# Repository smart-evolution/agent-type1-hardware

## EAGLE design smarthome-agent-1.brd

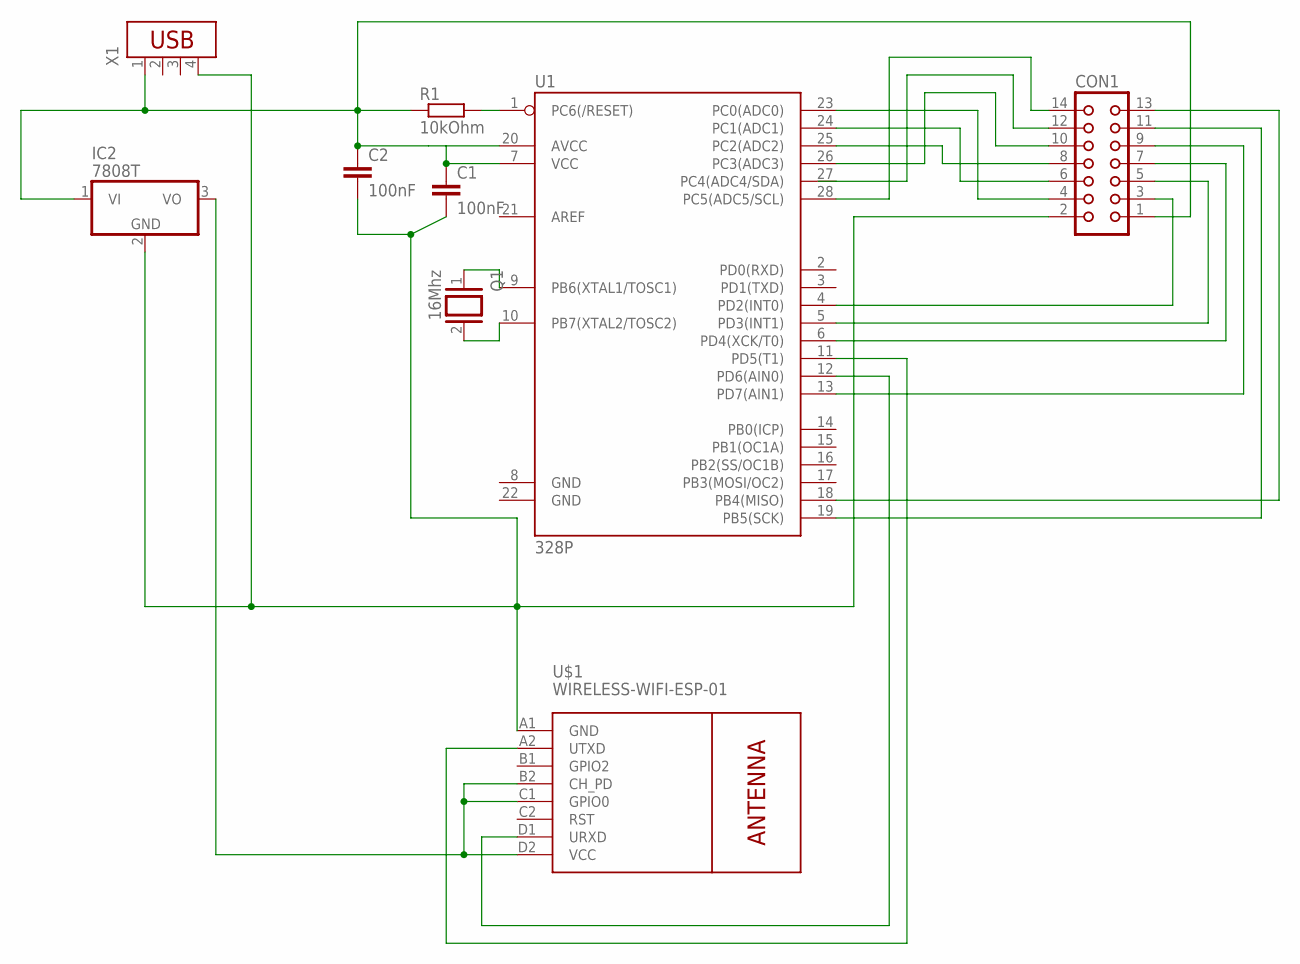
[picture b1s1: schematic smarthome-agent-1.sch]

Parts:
C1, C2: 100nF; C025-024X044
CON1: CON14
IC2: 7808T; TO220H
Q1: 16Mhz; QS
R1: 10kOhm; 0204/7
U1: 328P; DIP28
U$1: WIRELESS-WIFI-ESP-01
X1: USB-787616; USB

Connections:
unnamed: R1.2, U1.1 (PC6(/RESET))
unnamed: IC2.3 (VO), U$1.B2 (CH_PD), U$1.C1 (GPIO0), U$1.D2 (VCC)
unnamed: Q1.2, U1.10 (PB7(XTAL2/TOSC2))
unnamed: Q1.1, U1.9 (PB6(XTAL1/TOSC1))
unnamed: U1.11 (PD5(T1)), U$1.A2 (UTXD)
unnamed: U1.12 (PD6(AIN0)), U$1.D1 (URXD)
unnamed: CON1.10, U1.26 (PC3(ADC3))
unnamed: CON1.4, U1.23 (PC0(ADC0))
unnamed: CON1.6, U1.24 (PC1(ADC1))
unnamed: CON1.8, U1.25 (PC2(ADC2))
unnamed: CON1.12, U1.27 (PC4(ADC4/SDA))
unnamed: CON1.3, U1.4 (PD2(INT0))
unnamed: CON1.5, U1.5 (PD3(INT1))
unnamed: CON1.7, U1.6 (PD4(XCK/T0))
unnamed: CON1.9, U1.13 (PD7(AIN1))
unnamed: CON1.11, U1.19 (PB5(SCK))
unnamed: C1.1, C2.1, CON1.1, IC2.1 (VI), R1.1, U1.7 (VCC), U1.20 (AVCC), X1.1
unnamed: C1.2, C2.2, CON1.2, IC2.2 (GND), U$1.A1 (GND), X1.4
unnamed: CON1.13, U1.18 (PB4(MISO))
unnamed: CON1.14, U1.28 (PC5(ADC5/SCL))

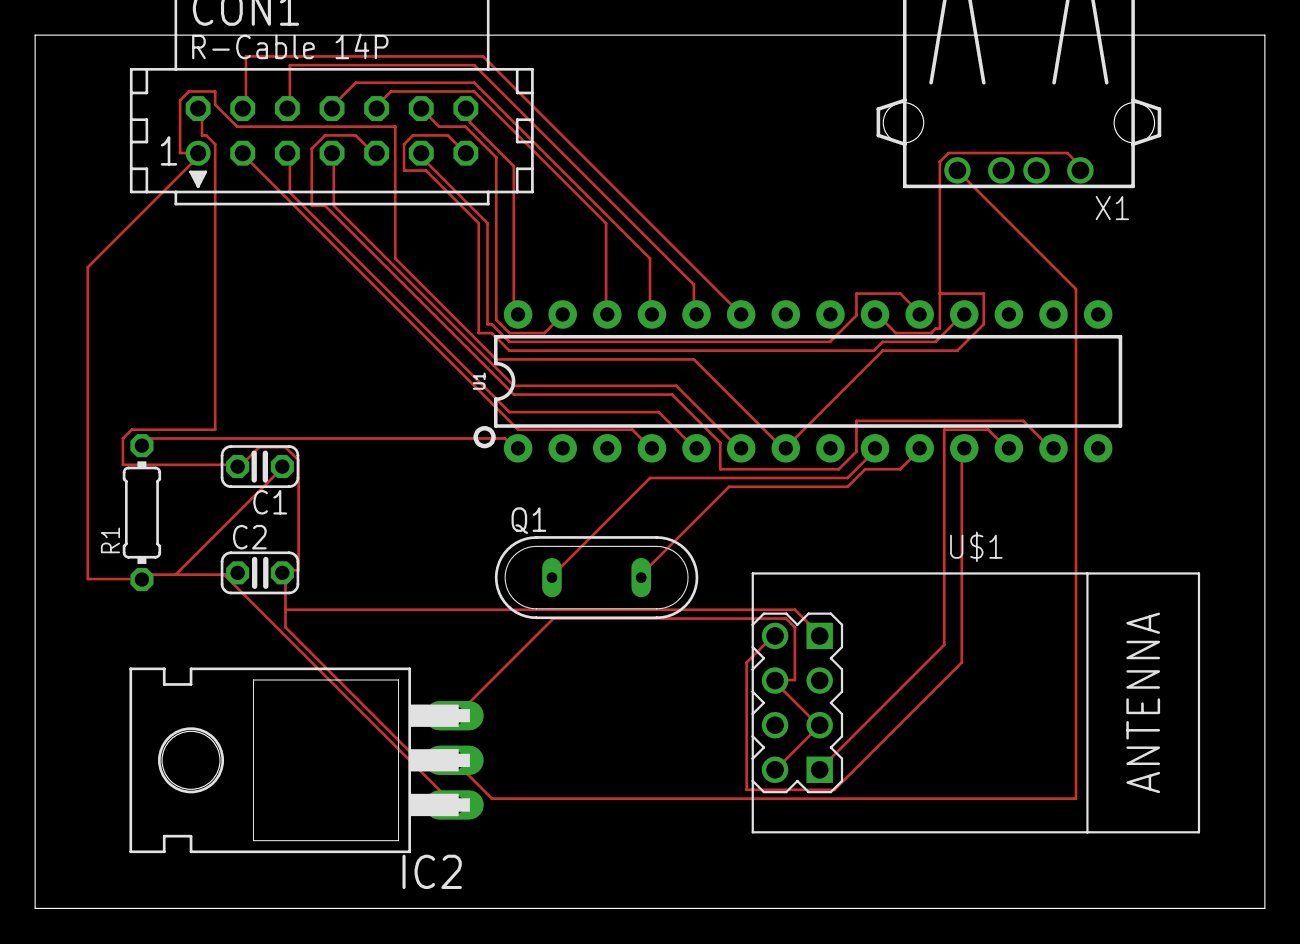
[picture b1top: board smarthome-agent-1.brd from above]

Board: 2 copper layers, 70.0 x 49.7 mm, 9 parts (0 on the bottom side), 20 nets.

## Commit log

2018-08-30 Add proper schema
2018-09-02 Add new elements
2018-09-03 Add ESP01
2018-09-08 Add board
2018-09-08 Update board to use one layer
2018-09-27 Add IDC socket and USB
2018-09-27 Update board routing
2018-10-18 HOME-49 - Cleanup circuit and board design for production
2018-10-21 Add gitignore
2018-10-21 HOME-49 - Cleanup circuit and board design for production (#1) (#2)

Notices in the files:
parts and their libraries:
diy-modules: Released under the Creative Commons Attribution 4.0 International License: http://creativecommons.org/licenses/by/4.0
SparkFun-IC-Microcontroller: Licensing: Creative Commons ShareAlike 4.0 International - https://creativecommons.org/licenses/by-sa/4.0
